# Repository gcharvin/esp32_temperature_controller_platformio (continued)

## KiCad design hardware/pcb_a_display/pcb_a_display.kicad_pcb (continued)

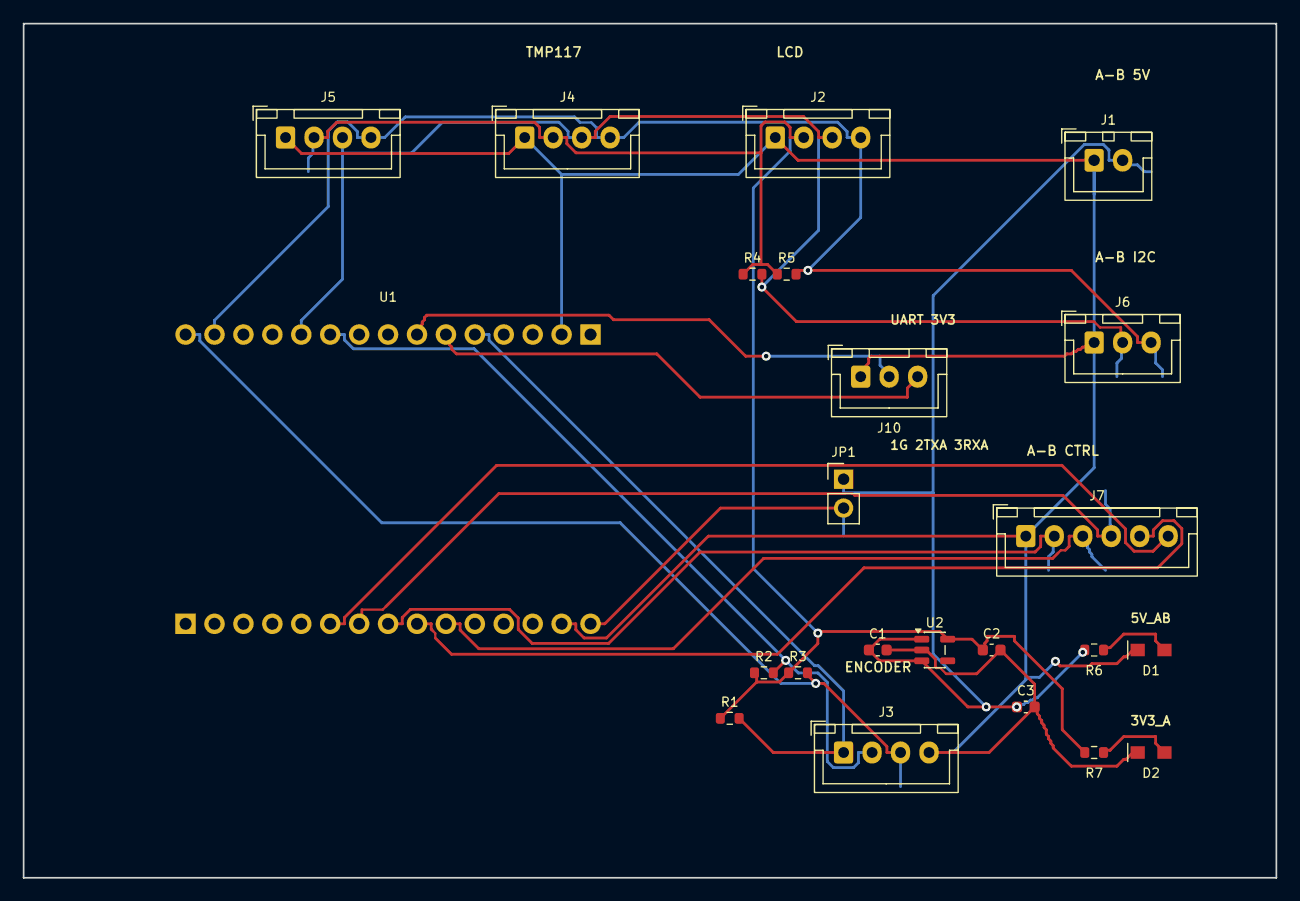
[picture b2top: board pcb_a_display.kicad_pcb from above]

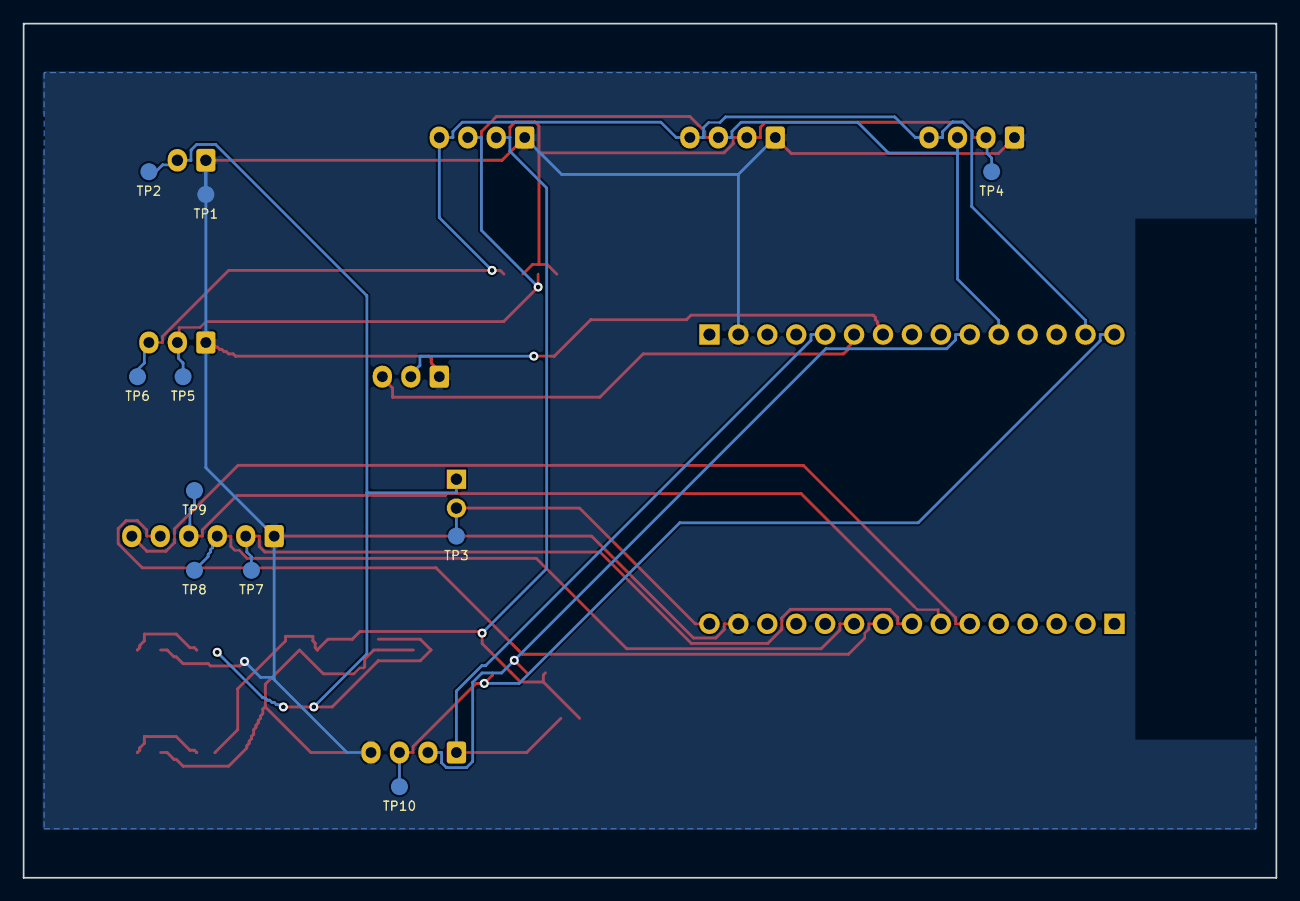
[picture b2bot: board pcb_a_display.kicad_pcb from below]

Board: 2 copper layers, 110.0 x 75.0 mm, 33 parts (10 on the bottom side), 18 nets.

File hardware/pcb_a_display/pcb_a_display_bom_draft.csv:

Reference,Value,Footprint,Design_Status,MPN,Manufacturer
C1,1uF,Capacitor_SMD:C_0603_1608Metric,ENGINEERING_SELECTED_STOCK_REVISION_2026_11_10,0603B105K160CT,Walsin
C2,1uF,Capacitor_SMD:C_0603_1608Metric,ENGINEERING_SELECTED_STOCK_REVISION_2026_11_10,0603B105K160CT,Walsin
C3,10uF,Capacitor_SMD:C_0603_1608Metric,ENGINEERING_SELECTED_STOCK_REVISION_2026_11_10,CL10A106KP8NNNC,Samsung
D1,APT2012LZGCK,LabHardware:LED_Kingbright_APT2012_Manufacturer,ENGINEERING_SELECTED_FOR_PROTOTYPE,APT2012LZGCK,Kingbright
D2,APT2012LZGCK,LabHardware:LED_Kingbright_APT2012_Manufacturer,ENGINEERING_SELECTED_FOR_PROTOTYPE,APT2012LZGCK,Kingbright
J1,A-B POWER / XH-2,Connector_JST:JST_XH_B2B-XH-A_1x02_P2.50mm_Vertical,ENGINEERING_SELECTED_FOR_PROTOTYPE,B2B-XH-A(LF)(SN),JST
J2,LCD20x4 + backpack / 3V3,Connector_JST:JST_XH_B4B-XH-A_1x04_P2.50mm_Vertical,ENGINEERING_SELECTED_FOR_PROTOTYPE,B4B-XH-A(LF)(SN),JST
J3,Encoder / A B SW GND,Connector_JST:JST_XH_B4B-XH-A_1x04_P2.50mm_Vertical,ENGINEERING_SELECTED_FOR_PROTOTYPE,B4B-XH-A(LF)(SN),JST
J4,TMP117 module / addr 0x48,Connector_JST:JST_XH_B4B-XH-A_1x04_P2.50mm_Vertical,ENGINEERING_SELECTED_FOR_PROTOTYPE,B4B-XH-A(LF)(SN),JST
J5,BH1750 module / addr 0x23,Connector_JST:JST_XH_B4B-XH-A_1x04_P2.50mm_Vertical,ENGINEERING_SELECTED_FOR_PROTOTYPE,B4B-XH-A(LF)(SN),JST
J6,A-B I2C / XH-3,Connector_JST:JST_XH_B3B-XH-A_1x03_P2.50mm_Vertical,ENGINEERING_SELECTED_FOR_PROTOTYPE,B3B-XH-A(LF)(SN),JST
J7,A-B CTRL / XH-6,Connector_JST:JST_XH_B6B-XH-A_1x06_P2.50mm_Vertical,ENGINEERING_SELECTED_FOR_PROTOTYPE,B6B-XH-A(LF)(SN),JST
JP1,5V DevKit link / remove for service,Connector_PinHeader_2.54mm:PinHeader_1x02_P2.54mm_Vertical,ENGINEERING_SELECTED_FOR_PROTOTYPE,M20-9990246,Harwin
R1,10k,Resistor_SMD:R_0603_1608Metric,ENGINEERING_SELECTED_FOR_PROTOTYPE,RC0603FR-0710KL,YAGEO
R2,10k,Resistor_SMD:R_0603_1608Metric,ENGINEERING_SELECTED_FOR_PROTOTYPE,RC0603FR-0710KL,YAGEO
R3,10k,Resistor_SMD:R_0603_1608Metric,ENGINEERING_SELECTED_FOR_PROTOTYPE,RC0603FR-0710KL,YAGEO
R4,4.7k,Resistor_SMD:R_0603_1608Metric,ENGINEERING_SELECTED_FOR_PROTOTYPE,RC0603FR-074K7L,YAGEO
R5,4.7k,Resistor_SMD:R_0603_1608Metric,ENGINEERING_SELECTED_FOR_PROTOTYPE,RC0603FR-074K7L,YAGEO
R6,1.5k / 1% / 0.1W,Resistor_SMD:R_0603_1608Metric,ENGINEERING_SELECTED_FOR_PROTOTYPE,RC0603FR-071K5L,YAGEO
R7,470R / 1% / 0.1W,Resistor_SMD:R_0603_1608Metric,ENGINEERING_SELECTED_FOR_PROTOTYPE,RC0603FR-07470RL,YAGEO
U1,ESP32 USB-C / 30P user module,LabHardware:ESP32_30P_HCTL_PM254_Rows25.40mm,NOT_A_FACTORY_PURCHASED_NATIVE_PART,,Customer supplied
U2,AP2112K-3.3 peripherals,Package_TO_SOT_SMD:SOT-23-5,ENGINEERING_SELECTED_FOR_PROTOTYPE,AP2112K-3.3TRG1,Diodes Incorporated
TP1,GND,LabHardware:ProbePad_D1.5mm_NoPaste,COPPER_ONLY_TEST_POINT,,
TP2,+5V_AB,LabHardware:ProbePad_D1.5mm_NoPaste,COPPER_ONLY_TEST_POINT,,
TP3,+5V_DEVKIT,LabHardware:ProbePad_D1.5mm_NoPaste,COPPER_ONLY_TEST_POINT,,
TP4,+3V3_A,LabHardware:ProbePad_D1.5mm_NoPaste,COPPER_ONLY_TEST_POINT,,
TP5,I2C_SDA,LabHardware:ProbePad_D1.5mm_NoPaste,COPPER_ONLY_TEST_POINT,,
TP6,I2C_SCL,LabHardware:ProbePad_D1.5mm_NoPaste,COPPER_ONLY_TEST_POINT,,
TP7,PWM0,LabHardware:ProbePad_D1.5mm_NoPaste,COPPER_ONLY_TEST_POINT,,
TP8,ENABLE,LabHardware:ProbePad_D1.5mm_NoPaste,COPPER_ONLY_TEST_POINT,,
TP9,FAULT_N,LabHardware:ProbePad_D1.5mm_NoPaste,COPPER_ONLY_TEST_POINT,,
TP10,ENC_SW,LabHardware:ProbePad_D1.5mm_NoPaste,COPPER_ONLY_TEST_POINT,,
J10,A-B UART / 3V3 / GND TX_A RX_A,Connector_JST:JST_XH_B3B-XH-A_1x03_P2.50mm_Vertical,ENGINEERING_SELECTED_FOR_PROTOTYPE,B3B-XH-A(LF)(SN),JST

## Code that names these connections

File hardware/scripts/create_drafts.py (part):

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CUSTOM = {}
CUSTOM['DevKit_Interface'] = module('DevKit_Interface', [
    ('5V','5V','power_in','L'), ('GND','GND','power_in','L'),
    ('21','GPIO21 SDA','bidirectional','L'),('22','GPIO22 SCL','output','L'),
    ('4','GPIO4 ENC_A','input','L'),('19','GPIO19 ENC_B','input','L'),('23','GPIO23 ENC_SW','input','L'),
    ('25','GPIO25 PWM0','output','R'),('26','GPIO26 PWM1','output','R'),
    ('27','GPIO27 ENABLE','output','R'),('32','GPIO32 DIN0','input','R'),('33','GPIO33 FAULT_N','input','R')], 40.64)
CUSTOM['Buck_Module_TBD'] = module('Buck_Module_TBD', [('1','VIN+','power_in','L'),('2','VIN-','power_in','L'),('3','5V OUT+','power_out','R'),('4','OUT-','passive','R')])
CUSTOM['NMOS_TBD'] = module('NMOS_TBD', [('1','GATE','input','L'),('2','DRAIN','passive','R'),('3','SOURCE','passive','R')],20.32)

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        {'pin':2,'net':'+5V_AB','direction':'B->A'}]},
    {'reference':'J6','function':'I2C bus, no power rail','pins':[
        {'pin':1,'net':'GND','direction':'common'},
        {'pin':2,'net':'I2C_SDA','direction':'bidirectional'},
        {'pin':3,'net':'I2C_SCL','direction':'A->B'}]},
    {'reference':'J7','function':'Control and reserved signals','pins':[
        {'pin':1,'net':'GND','direction':'common'},
        {'pin':2,'net':'PWM0','direction':'A->B'},
        {'pin':3,'net':'ENABLE','direction':'A->B'},
        {'pin':4,'net':'FAULT_N','direction':'B->A, open-drain active-low'},
        {'pin':5,'net':'PWM1','direction':'A->B','connected_on_b':False},
        {'pin':6,'net':'DIN0','direction':'B->A','connected_on_b':False}]}]

def add_interface(sheet, positions):
    for port, (x,y) in zip(INTERFACE, positions):
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    s.add('Device:Fuse','F1','TBD current',85,45,{'1':'VIN_RAW','2':'VIN_FUSED'},'',rotation=90)
    s.add('Device:D_Schottky','D1','Reverse polarity / TBD rating',150,45,{'1':'VIN_PROTECTED','2':'VIN_FUSED'},'',rotation=0)
    s.add('Device:D_TVS','D2','TVS TBD',220,45,{'1':'GND','2':'VIN_PROTECTED'},'',rotation=90)
    s.add('Lab:Buck_Module_TBD','U1','12V -> 5V module / TBD',300,45,{'1':'VIN_PROTECTED','2':'GND','3':'+5V_AB','4':'GND'},status='Logical interface only; rating, pinout and footprint TBD')
    s.text(20,75,'F1, D1, D2, U1 and Q1 require load current / transient / thermal sizing. D1 is a series diode, with conduction losses.\n12 V prototype only. No 24 V qualification. Main load returns directly to input GND; keep analog ground paths quiet.')
    s.section(20,98,'B2 - PASSIVE MODULE INTERFACE / LOCAL 3.3 V')
    add_interface(s,[(40,123),(90,123),(150,125)])
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
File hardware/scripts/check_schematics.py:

"""Export and check the actual KiCad schematics, including the A/B cable contract.

Example (KiCad Python, or any Python >=3.10):
  python hardware/scripts/check_schematics.py --kicad-cli <path-to-kicad-cli>
This never regenerates or changes the source schematics.
"""
import argparse
import json
from pathlib import Path
import shutil
import subprocess
import xml.etree.ElementTree as ET

ROOT = Path(__file__).resolve().parents[1]

def run(*args):
    subprocess.run([str(a) for a in args],check=True)

def read_netlist(path):
    pins={}
    groups={}
    root=ET.parse(path).getroot()
    for net in root.findall('./nets/net'):
        name=net.attrib['name'].removeprefix('/')
        nodes={(n.attrib['ref'],n.attrib['pin']) for n in net.findall('node')}
        groups[name]=nodes
        for node in nodes:
            if node in pins:
                raise AssertionError(f'Pin appears on two nets: {node}')
            pins[node]=name
    return pins,groups

def check_pin(pins, ref, pin, expected):
    actual=pins.get((ref,str(pin)))
    assert actual == expected, f'{ref}.{pin}: expected {expected}, got {actual}'

def check_nc(pins,groups,ref,pin):
    net=pins[(ref,str(pin))]
    assert net.startswith('unconnected-') and len(groups[net]) == 1, (ref,pin,net)

def main():
    parser=argparse.ArgumentParser(description=__doc__)
    parser.add_argument('--kicad-cli',default=shutil.which('kicad-cli') or 'C:/Program Files/KiCad/10.0/bin/kicad-cli.exe')
    args=parser.parse_args()
    out=ROOT/'review'
    out.mkdir(exist_ok=True)
    boards={}
    for name in ('pcb_a_display','pcb_b_temperature'):
        source=ROOT/name/(name+'.kicad_sch')
        run(args.kicad_cli,'sch','erc',source,'--output',out/(name+'_erc.rpt'),'--exit-code-violations')
        run(args.kicad_cli,'sch','export','netlist','--format','kicadxml','--output',out/(name+'.net.xml'),source)
        run(args.kicad_cli,'sch','export','pdf','--output',out/(name+'.pdf'),source)
        boards[name]=read_netlist(out/(name+'.net.xml'))
    contract=json.loads((ROOT/'interface_ab.json').read_text(encoding='utf-8'))
    for name,(pins,groups) in boards.items():
        exported=ET.parse(out/(name+'.net.xml')).getroot()
        footprints={c.attrib['ref']: c.findtext('footprint') for c in exported.findall('./components/comp')}
        for port in contract['connectors']:
            ref=port['reference']; count=len(port['pins'])
            assert {p for r,p in pins if r==ref} == {str(row['pin']) for row in port['pins']}, (name,ref,'unexpected pin count')
            expected_fp=f'Connector_JST:JST_XH_B{count}B-XH-A_1x{count:02d}_P2.50mm_Vertical'
            assert footprints.get(ref)==expected_fp, (name,ref,'wrong JST footprint')
            for row in port['pins']:
                if row['net'] is None or (name=='pcb_b_temperature' and not row.get('connected_on_b',True)):
                    check_nc(pins,groups,ref,row['pin'])
                else:
                    check_pin(pins,ref,row['pin'],row['net'])
            assert all(not n.startswith(('VIN','+3V3')) and n!='HEATER_LOW' for (r,_),n in pins.items() if r==ref)
        assert {n for (r,_),n in pins.items() if r=='J1'} == {'GND','+5V_AB'}
        assert {n for (r,_),n in pins.items() if r=='J6'} == {'GND','I2C_SDA','I2C_SCL'}
    a,ag=boards['pcb_a_display']; b,bg=boards['pcb_b_temperature']
    # Physical 30-contact socket numbering; GPIO labels are not pad numbers.
    for pin,net in [(15,'+5V_DEVKIT'),(14,'GND'),(17,'GND'),(26,'I2C_SDA'),(29,'I2C_SCL'),(8,'PWM0'),(9,'PWM1'),(10,'ENABLE'),(6,'DIN0'),(7,'FAULT_N'),(20,'ENC_A'),(25,'ENC_B'),(30,'ENC_SW'),(21,'UART_A_RX'),(22,'UART_A_TX')]:
        check_pin(a,'U1',pin,net)
    assert ag['UART_A_TX']=={('U1','22'),('J10','2')}
    assert ag['UART_A_RX']=={('U1','21'),('J10','3')}
    check_nc(b,bg,'J10',2);check_nc(b,bg,'J10',3)
    check_pin(a,'JP1',1,'+5V_AB');check_pin(a,'JP1',2,'+5V_DEVKIT')
    check_pin(a,'U2',5,'+3V3_A');check_pin(a,'J2',2,'+3V3_A')
    for pin,net in [(1,'+3V3_B'),(8,'+3V3_B'),(3,'GND'),(4,'NTC_ADC'),(9,'I2C_SDA'),(10,'I2C_SCL'),(2,'FAULT_N')]:
        check_pin(b,'U4',pin,net)
    for ref,pin,net in [('U3',1,'PWM0'),('U3',2,'ENABLE'),('U3',4,'GATE_CMD'),('Q1',1,'GATE'),('Q1',2,'HEATER_LOW'),('Q1',3,'PGND'),('J3',1,'VIN_PROTECTED'),('J3',2,'HEATER_LOW'),('Q2',2,'VIN_FUSED'),('Q2',3,'VIN_PROTECTED'),('Q2',1,'REV_GATE'),('D3',1,'VIN_PROTECTED'),('D3',2,'REV_GATE'),('D4',1,'VIN_PROTECTED'),('D4',2,'HEATER_LOW'),('F1',1,'VIN_RAW'),('F1',2,'VIN_FUSED'),('F2',1,'+5V_BUCK'),('F2',2,'+5V_AB'),('U5',1,'+5V_AB'),('U5',2,'PGND'),('U5',3,'GATE_CMD'),('U5',4,'PGND'),('U5',5,'GATE_DRV'),('C8',1,'VIN_PROTECTED'),('C8',2,'PGND'),('R5',1,'NTC_RAW'),('R5',2,'GND'),('R6',1,'NTC_RAW'),('R6',2,'NTC_ADC')]:
        check_pin(b,ref,pin,net)
    assert bg['GND'].isdisjoint(bg['PGND']), 'Retain separately routed logic/power returns joined only by NT1'
    for ref,pin,net in [('U1',1,'VIN_PROTECTED'),('U1',2,'BUCK_SW'),('U1',3,'PGND'),('U1',4,'+5V_BUCK'),('U1',5,'PGND'),('L1',1,'BUCK_SW'),('L1',2,'+5V_BUCK'),('D9',1,'BUCK_SW'),('D9',2,'PGND'),('C9',1,'VIN_PROTECTED'),('C9',2,'PGND'),('C10',1,'+5V_BUCK'),('C10',2,'BUCK_CAP_RETURN'),('R13',1,'BUCK_CAP_RETURN'),('R13',2,'PGND'),('NT1',1,'PGND'),('NT1',2,'GND')]:
        check_pin(b,ref,pin,net)
    assert not any(ref in ['J8','J9'] for ref,pin in b), 'External buck wiring must be removed'
    bc={c.attrib['ref']:c for c in ET.parse(out/'pcb_b_temperature.net.xml').getroot().findall('./components/comp')}
    assert bc['U1'].findtext('value')=='LM2596S-5.0/NOPB'
    assert bc['U1'].findtext('footprint')=='Package_TO_SOT_SMD:TO-263-5_TabPin3'
    assert bc['L1'].findtext('value').startswith('100uH') and bc['C10'].findtext('value').startswith('330uF') and bc['R13'].findtext('value').startswith('50m')
    # Independent diagnostic contract: check rail, series resistor, LED polarity
    # and return. In particular, HEAT must follow the enabled driver output and
    # no indicator may load the NTC divider or add another PGND-to-GND connection.
    diagnostics=[]
    contracts={
        'pcb_a_display': [('D1','R6','+5V_AB','GND','1.5k'),('D2','R7','+3V3_A','GND','470R')],
        'pcb_b_temperature': [('D5','R9','VIN_PROTECTED','PGND','15k'),('D6','R10','+5V_AB','GND','1.5k'),
                              ('D7','R11','+3V3_B','GND','470R'),('D8','R12','GATE_DRV','PGND','2.2k')]}
    for name,rows in contracts.items():
        pins,groups=boards[name]
        comps={c.attrib['ref']:c for c in ET.parse(out/(name+'.net.xml')).getroot().findall('./components/comp')}
        for led,resistor,rail,ground,resistance in rows:
            check_pin(pins,resistor,1,rail);check_pin(pins,led,1,ground)
            series=pins[(resistor,'2')]
            assert groups[series]=={(resistor,'2'),(led,'2')},(led,'wrong series chain')
            assert comps[resistor].findtext('value').split(' / ')[0]==resistance
            assert comps[led].findtext('footprint')=='LabHardware:LED_Kingbright_APT2012_Manufacturer'
            assert comps[led].findtext('value')==('APT2012LSYCK/J3-PRV' if led=='D8' else 'APT2012LZGCK')
            diagnostics.append(dict(board=name,led=led,resistor=resistor,supply=rail,return_net=ground,
                                    series_only=True,cathode_pin=1,anode_pin=2))
    check_pin(b,'J4',1,'+3V3_B');check_pin(b,'J4',2,'NTC_RAW')
    assert bg['NTC_RAW']=={('J4','2'),('R5','1'),('R6','1'),('TP6','1')},'Only the copper probe may be added to the NTC divider'
    (out/'routing/diagnostic_validation.json').write_text(json.dumps(dict(LEDs=diagnostics,
        NTC_divider_unloaded=True,HEAT_measures='gate driver output, not heater current'),indent=2)+'\n',encoding='utf-8')
    for name,groups in [('A',ag),('B',bg)]:
        allowed_rails={'+3V3_A'} if name=='A' else {'+3V3_B'}
        assert allowed_rails.issubset(groups)
        other_rail='+3V3_B' if name=='A' else '+3V3_A'
        assert other_rail not in groups
    summary='Both schematics: ERC 0 errors / 0 warnings.\nA/B interface, isolated supply rails, ADC address strap, heater enable/gate, NTC and power path checked against exported netlists.\nSix diagnostic LED series chains, polarity, rail/return assignments and unloaded NTC divider verified.\nThese checks do not qualify current ratings, footprints, PCB routing or safety.\n'
    (out/'validation.txt').write_text(summary,encoding='utf-8')
    print(summary)

if __name__=='__main__':
    main()

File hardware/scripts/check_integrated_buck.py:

"""Bind the real PCB B netlist/geometry to the separately simulated buck study."""
import hashlib,json,re,subprocess
from pathlib import Path
import xml.etree.ElementTree as ET
import pcbnew as p

ROOT=Path(__file__).resolve().parents[1]
def sha(path):return hashlib.sha256(path.read_bytes()).hexdigest()
def main():
 name='pcb_b_temperature';source=ROOT/name/(name+'.kicad_pcb');board=p.LoadBoard(str(source))
 xml=ET.parse(ROOT/'review'/f'{name}.net.xml').getroot()
 comps={v.attrib['ref']:v for v in xml.findall('./components/comp')}
 pins={(n.attrib['ref'],n.attrib['pin']):net.attrib['name'].removeprefix('/') for net in xml.findall('./nets/net') for n in net.findall('node')}
 assert comps['U1'].findtext('value')=='LM2596S-5.0/NOPB'
 assert 'J8' not in comps and 'J9' not in comps
 for ref,pin,net in [('U1','1','VIN_PROTECTED'),('U1','2','BUCK_SW'),('U1','3','PGND'),('U1','4','+5V_BUCK'),('U1','5','PGND'),('NT1','1','PGND'),('NT1','2','GND')]:assert pins[ref,pin]==net
 assert comps['C8'].findtext('value').startswith('100uF')
 assert comps['C9'].findtext('value').startswith('100nF')
 assert comps['L1'].findtext('value').startswith('100uH')
 assert comps['C10'].findtext('value').startswith('330uF')
 assert comps['R13'].findtext('value').startswith('50m')
 assert comps['R13'].findtext('./fields/field[@name="MPN"]')=='WSL1206R0500FEA'
 assert comps['C10'].findtext('./fields/field[@name="MPN"]')=='EEUFS1V331LB'
 assert {k for k,n in pins.items() if n=='BUCK_CAP_RETURN'}=={('C10','2'),('R13','1')}
 fps={f.GetReference():f for f in board.GetFootprints()}
 # Connector origins are the v0.4 mechanical contract, in native mm.
 for ref,expected in {'J1':(75,110),'J2':(69,67),'J3':(135,67),'J4':(141,107),'J6':(93,110),'J7':(113,110)}.items():
  pt=fps[ref].GetPosition();assert (p.ToMM(pt.x),p.ToMM(pt.y))==expected
 assert '1,2' in source.read_text() or 'net_tie_pad_groups' in source.read_text()
 study=ROOT/'power_study/lm2596'
 binding_path=study/'current_acceptance.json';binding=json.loads(binding_path.read_text())
 assert binding['C10']=='EEUFS1V331LB' and binding['R13']=='WSL1206R0500FEA' and binding['R13_ohm']==.05
 for relative,digest in binding['source_sha256'].items():assert sha(ROOT/relative)==digest,'Stale buck qualification '+relative
 planpath=ROOT/binding['plan'];plan=json.loads(planpath.read_text())
 resultpath=ROOT/binding['results'];results=json.loads(resultpath.read_text())
 assert results['all_criteria_pass'] and len(results['cases'])==7
 assert plan['external_components']['Cout_added_series_resistance_ohm']==.05
 assert plan['external_components']['Cout_lower_series_bound_ohm']==.049
 for case in results['cases']:
  assert sha(planpath.parent/case['deck'])==case['deck_sha256']
  assert case['all_criteria_pass'] and case['inputs_hashed_at_run_start']
 # New startup core adds the actual local bypass. ESR/DCR are modeled losses,
 # not extra BOM parts. Upstream/PCB parasitics are deliberately not included.
 deck=study/'benches/integrated_B_startup.cir'
 base=(study/'benches/startup.cir').read_text()
 deck.write_text(base.replace('LM2596 fixed 5 V - startup', 'LM2596 core from PCB B v0.5 exported netlist - startup')
                 .replace('CIN vin cinret 100u', 'CIN vin cinret '+comps['C8'].findtext('value').split('F')[0])
                 .replace('COUT vout esr 330u', 'COUT vout esr '+comps['C10'].findtext('value').split('F')[0])
                 .replace('L1 sw lind 100u', 'L1 sw lind '+comps['L1'].findtext('value').split('H')[0])
                 .replace('.options ', 'CLOCAL vin 0 '+comps['C9'].findtext('value').split('F')[0]+'\n.options '),encoding='utf-8')
 report=dict(revision='PCB B 0.5.3 integrated LM2596 stock alternatives',
   source_sha256={str(path.relative_to(ROOT)):sha(path) for path in [source,source.with_suffix('.kicad_sch'),ROOT/'review'/f'{name}.net.xml',binding_path,planpath,resultpath]},
   dimensions_mm=[90,65,1.6],copper_um=70,connector_positions_preserved=True,
   external_buck_removed=True,ground_star='NT1 copper only, PGND pin1 / logic GND pin2',
   output_budget_A=.8,fuse_F2_A=1,acceptance_study_cases_passed=7,
   core_deck=str(deck.relative_to(ROOT)),core_deck_sha256=sha(deck),
   limits=['Core simulation excludes PCB/cable parasitics, upstream protection, thermal and heater coupling.',
           'Capacitor maximum impedance41mOhm plus physical R13 50mOhm approximated conservatively as100mOhm total; separate49mOhm lower and180mOhm upper stress cases passed.',
           'Current STEP fit checked separately against B v0.5; real cable, clip and thermal tests pending.',
           'R13/C9 purchasing candidates documented; R13 manufacturer land pattern checked separately. Supplier approval and physical startup/thermal/fault tests pending.'])
 (ROOT/'review/routing/integrated_buck_validation.json').write_text(json.dumps(report,indent=2)+'\n',encoding='utf-8')
 print(json.dumps(report,indent=2))

if __name__=='__main__':main()

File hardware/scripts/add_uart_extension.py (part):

"""Incrementally add J10 UART to native A/B, preserving existing copper.

KiCad Python --apply. A: GPIO17 TX / GPIO16 RX. B temperature: pins2/3 NC,
reserved for future B functions. Native J8/J9 remain free for socket upload aliases.
"""
import argparse
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    for sub in s.children(symbol,'symbol'):
        for pin in s.children(sub,'pin'):
            if s.unquote(s.child(pin,'number')[1])=='22':
                assert s.unquote(s.child(pin,'name')[1])=='GPIO17'
                pin[1]='output'


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    sheet.section(20,base,'UART EXTENSION - J10 - 3.3 V LOGIC, NOT RS232 VOLTAGE LEVELS')
    sheet.connector('J10',VALUE,65,base+25,['GND','UART_A_TX','UART_A_RX'] if is_a else ['GND',None,None],3,FP)
    sheet.text(110,base+18,'1 GND / 2 TX_A -> RX_B / 3 RX_A <- TX_B. Straight cable; no supply rail.',1.2)
    sheet.text(110,base+27,('A: GPIO17 TX (U1.22), GPIO16 RX (U1.21); independent of USB UART0 and PWM.' if is_a else
        'B temperature: contacts 2 and 3 intentionally NC; connector fitted for interface compatibility.'),1.2)
    sheet.text(110,base+36,'Reserved extension; future B must implement its UART peripheral/transceiver. No hot-plug.',1.2)
    for item in sheet.items:
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        scope='70 physical native PCB components; excludes virtual ESP32, copper net tie and22 copper test pads; sockets and shunt separate')
    selection.write_text(json.dumps(choices,indent=2,ensure_ascii=False)+'\n',encoding='utf-8')
    modulepath=ROOT/'module_selection.json';modules=json.loads(modulepath.read_text(encoding='utf-8'))
    modules['devkit']['used_pin_nets'].update({'21':'UART_A_RX','22':'UART_A_TX'})
    modules['revision']='A0.4.2 / B0.5.2 UART, original power topology'
    modulepath.write_text(json.dumps(modules,indent=2,ensure_ascii=False)+'\n',encoding='utf-8')
    interfacepath=ROOT/'interface_ab.json';interface=json.loads(interfacepath.read_text(encoding='utf-8'))
    interface['revision']='0.4 / dedicated UART J10 / A0.4.2 B0.5.2'
    interface['harness']='three required cables plus optional reserved UART cable; straight-through; connections unpowered, no hot-plug'
    interface['connectors'].append(dict(reference='J10',function='Dedicated 3.3V UART; optional on temperature prototype',required_for_temperature=False,
        pins=[dict(pin=1,net='GND',direction='common'),dict(pin=2,net='UART_A_TX',direction='A->future B RX',gpio_on_a=17,connected_on_b=False),
              dict(pin=3,net='UART_A_RX',direction='future B TX->A',gpio_on_a=16,connected_on_b=False)]))
    interfacepath.write_text(json.dumps(interface,indent=2,ensure_ascii=False)+'\n',encoding='utf-8')
    (ROOT/'review/uart_extension_copper_baseline.json').write_text(json.dumps(dict(backup=str(backup),boards=preserved),indent=2)+'\n',encoding='utf-8')
    from add_test_points import refresh_placement
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
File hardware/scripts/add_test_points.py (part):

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        for i,(net,anchorref,anchorpin) in enumerate(items,1):
            target=next(pad for pad in data['pads'] if pad['ref']==anchorref and pad['pin']==anchorpin)
            assert target['net']=='/'+net,(name,net,target)
            ref='TP'+str(i);label=ref+' '+net.replace('I2C_','').replace('VIN_PROTECTED','VIN24').replace('+5V_DEVKIT','VIN5').replace('+5V_BUCK','5VBUCK').replace('GATE_DRV','GATE')
            at=choose_position([target['x'],target['y']],label,'/'+net,data,used,spec)
            fp=p.FootprintLoad(LIB,'TestPoint_Pad_D1.5mm');fp.SetReference(ref);fp.SetValue(net);fp.SetPosition(pos(*at));board.Add(fp)
            fp.Flip(fp.GetPosition(),False);fp.SetFPID(p.LIB_ID('TestPoint','TestPoint_Pad_D1.5mm'))
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
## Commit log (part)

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2025-12-23 test update
2026-01-08 integrated LCD I2C component
2026-02-11 with part list
2026-02-12 refactor pour séparation UI / métier
2026-02-12 fixed room sensor
